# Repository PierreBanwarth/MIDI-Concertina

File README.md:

# MIDI-concertina

This is The Github project wich his a personnal work about Making an electronic version of my concertina,

Goal is to play by night with my headphones for my neighboors and maybe with my band BernyTradSchool

Arduino =>( midi library ) Serial port ( hairless midi serial ) => midi port ( loopMidi ) => Fruity Loops / Ableton / ...

We chose this solution because it's the most generic you can interface with

I use two arduinos (nano)

this project is developed with platformIO file structure.
http://platformio.org/

After the V1 done (whithout air sensor) it's look my buttons was very bad and not speed enough to play music so i have ordered some Cherry mx black keys

I have done my custom keyboard here
http://www.keyboard-layout-editor.com/#/

and use it to create the grid to plate mounted switches
http://builder.swillkb.com/

I've write tutorials here :

In english
https://www.instructables.com/id/Make-Your-MIDI-Accordion/
In french
https://ouiaremakers.com/posts/tutoriel-diy-creation-d-un-accordeon-midi

Some personnal note in french about the new version

# Le projet : petit historique
Je suis developpeur et je joue du concertina et j'aime cet instrument inventé par un physicien (https://fr.wikipedia.org/wiki/Charles_Wheatstone)

Le problème initial était de pouvoir jouer au casque la nuit et ainsi laisser ma copine dormir.

## Electronique :
Dans cet objectif la j'ai acheté mon premier Arduino à noel 2016.

Avec cet objectif en tête je me suis dabord entrainé sur un controlleur de vole spatiaux pour le jeu Kerbal Space Program.

[PHOTO DE LA BOITE EN CARTON]

ça m'a permis de comprendre le branchement des boutons et la récupération des entrée/sortie dans le code.

J'ai ensuite réalisé un premier prototype de concertina MIDI

[PHOTO DU premier PROTOTYPE]

à l'époque je n'avais pas en tête l'utilisation du protocole MIDI je sortais donc le son en 8bit sur une sortie casque.

## Le clavier et les Boutons :

Depuis le début du projet le choix a été fait de ne pas faire de matrice de boutons.

Le but est de reproduire le plus fidèlement possible le jeux sur l'instrument (dans un premier temps son clavier au moins)

Hors le multipléxage ne permet pas de jouer plusieurs notes en même temps de façon continue.

Si je tape sur 6 touches je veux obtenir six sons différents.

Hors quand on tape sur six touches de son clavier d'ordinateur simultanément : on obtiens une seul frappe.

(peut etre a mieux expliquer)

Donc chaque sortie de l'arduino sera dédié a une touche.

### Premiers boutons :

[PHOTO Des premiers boutons]

Cependant les boutons etait bas de gamme et ne reagissais parfois pas du tout a l'appuie.

Hors ce projet necessite des boutons réactifs et précs.

### CHERRY MX
Je ne me souviens pas si c'est moi ou si on m'a soufflé l'idée mais c'est vrai que les boutons de claviers mécaniques ont plusieurs avantages :

Une communauté active qui a crée :
- Des PCB personnalisés.
- Les "Footprint" des divers boutons.
- beaucoup de comparatifs des différents boutons.
- Des utilitaires en lignes comme :
http://www.keyboard-layout-editor.com/#/
http://builder.swillkb.com/
- Des lubrifiants, ressorts alternatifs et autres silencieux (en cours d'études)

L'avantage de ces switchs c'est qu'ils sont fait pour durer dans le temps, sont fiable et précis.

De plus ils ont un "top" qui permet d'adapter tout et n'importe quoi sur le dessus :

étude en cours :
- boutons de clavier :
- boutons style accordéon :
- bontons style concertina :

Merci beaucoup à toutes la communauté de Geekhack et de Reddit/CustomKeyboard pour toutes les heures de lectures.

J'ai donc fait un premier clavier (sans soufflet) qui ressemble aux claviers coupés en deux

[PHOTO DE LA VERSION 2]

Soucis rencontrés avec ce modèle : le clavier etait souder sans PCB donc par des cables.

Au niveau du temps et des manipulations ça s'est averé plutot fragile (malgré l'intervention d'un ami electronicien)

L'avantage du clavier de CONCERTINA-MIDI-V3 c'est que le PCB va finir de stabiliser les boutons

## Note sur le soufflet :
N'ayant qu'un seul concertina à cet époque la j'ai eu plusieurs idée de réalisation de soufflet custom.

Cependant devant la complexité de la chose j'ai décidé de ne pas gérer le soufflet dans un premier temps et d'utiliser un bouton à la place pour simuler le pousser/tirer.

* footswitch (pédale de guitare) : trop dur pour la main
* Bouton d'arcade : pas mal mais placé au mauvais endroit (sous la paume)
* Joystick : contre intuitif mais interessant de par les deux axes (mais on sort de l'idée de reproduction d'accordéon.)
* Cherry MX : parce que finalement c'est les meilleurs boutons qu'on puisse trouver j'ai réussi a en placer un sous mon pouce et c'etait plutôt efficace.

Cependant en 2017 j'ai acheté un nouveau concertina. Me laissant du coup l'ancien modèle libre. On en reparlera quand on evoquera l'impression 3D

## OPEN SOURCE MIDI :

Attiré depuis le début par la réalisation d'un projet a 100% Open Source et Open Hardware

Concernant le protocole MIDI j'ai entendu des choses sur des protocoles plus récent et peut être plus adapté a mon besoin.

Cependant je n'ai pas eu l'occasion ni le temps de me pencher sur ces solutions

With MIDILibrary (very easy to use for outputs)
http://playground.arduino.cc/Main/MIDILibrary

Good for interface with a virtual midi port and to test while developing
http://projectgus.github.io/hairless-midiserial/

to test and interface with Hairless Midi <-> Serial
http://www.tobias-erichsen.de/software/loopmidi.html

## RASPBERRY AS MIDI SYNTH.

Après la version 2.0 j'ai appris quelques morceaux les nuits d'insomnie, je me suis bien amusé a jouer de la guitare electrique et des sons MIDI vraiments moches

Cependant un nouveau besoin est arrivé, j'avais 2x45 minutes de trajets en bus par jour donc pourquoi pas profiter de ce temps "mort" pour jouer du concertina MIDI

J'ai donc cherché une solution et découvert que le Raspberry pouvait remplir la fonction de synthé MIDI.

Alors on ajoute une batterie pour alimenter le raspberry, On lance le démarrage du synthé MIDI, et on connect ça aux arduinos.

[Peut être mettre ici un tuto sur l'installation du synthé et son démarrage automatique]

plus qu'a choisir le son et on peux jouer en branchant un prise jack a la solution existante.

Cette version répond au besoin mais pause de nouvelles intérogations et ouvre un nouveau chant des possible

Nouveaux défi :
- laisser un raspberry dans la solution et permettre de brancher quand meme les deux mains de l'accordéon a un ordinateur
- intégrer la batterie a la solution => recharchement / boutons on/off

## NUMEROTATION DES VERSIONS ET MODELE ECONOMIQUE

Au fil de l'eau j'ai décidé d'un systême de notation des versions

les versions supérieurs verront un nouveau systême soit sur le clavier soit le soufflet voir les deux

et on passera a 3.5 sur une version portable (avec raspberry intégré)

J'ai réalisé qu'une seul main sans gestion du soufflet correspondais un petit clavier MIDI sans Matrice qui peux servir pour la musique electronique

Vu que le projet est Open Source vous n'aurez pas besoin de moi pour refaire tout de A à Z mais vous risquez d'y passer du temps.

J'ai donc opté pour une solution de vente du style Tyndie ou je vendrais
- le circuit imprimé
- le circuit imprimé + Arduino + Cherry MX + Boitier + vis etc..

https://www.tindie.com/

peut etre aussi une solution du style Pay me a coffee.

## GESTION DU SOUFFLE
  On a vu à travers l'impression 3D qu'on pouvais enfin sans abimer l'ancien concertina recreer des boitiers

  On peux donc placer un capteur de préssion.

  Mais on doit faire attention a la circulation de l'air :

    - attention a laisser passer de l'air (comme si on appuyais en permanence sur un bouton)

    - laisser passer de l'air implique une soupape (Gros trou ouvrable a l'aide d'un bouton pour reprendre ou relacher beaucoup d'air d'un coup)

# CONCERTINA MIDI V3.1
Le nouvelle version comporte deux avancés majeurs :
* gestion de l'air réaliste
* circuit imprimé pour les boutons et le BME280

## Impression 3D :
C'est en arrivant vivre à Rennes que j'ai découvert l'imprimante 3D d'un ami.
[PHOTO DU TRUMP 3D]

J'en ai acheté une peux de temps après, j'ai cependant fait l'erreure d'acheter une Geeetech I3 PRO B que je n'ai jamais vraiment réussi a maitriser.
[PHOTO DE MON IMPRIMANTE]

J'ai donc fini par prendre contact avec un imprimeur sur Rennes (https://www.hephaprint.fr/)

Au début l'idée c'était de faire une grille spécial pour mon nouveau concertina et c'etait l'occasion de faire connaissance :
[PHOTO DU CONCERTINA BLEU]

C'est un peu plus tard que je me suis rendu compte que si on pouvais imprimer le haut du boitier on pouvais du coup faire le bas

Et ainsi mettre le clavier déja réalisé dans une boite étanche et a la taille exact du soufflet.

Ce qui finalement nous permettrait de mettre un capteur de préssion pour gagner en réalisme.

Nous avons donc pris les côtes de mon premier concertina et réalisé un boitié en PET.
[PHOTO DE LA BOITE NOIRE]

## MY OWN PCB
Petit feedback sur la réalisation d'un circuit imprimé pour les boutonsn, le capteur de préssion et l'arduino

Tester c'est douter ?

J'ai réalisé deux plaques a l'heure ou j'ecrit ça et j'espere que la troisieme version sera la derniere.

Soucis de la première : Les boutons sont trop écartés et la plaque est trop grande

Soucis de la deuxième et de la premiere aussi du coup : Problème de branchement sur le capteur de préssion BME 280

Avant de réaliser un circuit bien penser a tester, je me suis fait un petit excès de confiance et ça m'a couté 40 balles

Pour réaliser le circuit je me suis inspiré de ça :
https://github.com/ruiqimao/keyboard-pcb-guide

Après sur l'utilisation de KiCad et LibreCad c'est long, dur, ingras.

Un peu compliqué de créer un circuit quand tu as rapidement bidouillé des Arduinos et que tu passes en mode ingenierie serieuse et définitive (20$ par essai).

la grande difficulté de ce projet c'est la maitrise des outils logiciels.

## Placer le circuit sur la grille du concertina.

Une fois le PCB crée il faut réaliser la grille en métal dans laquelle iront se loger les boutons
pour ça j'ai extrait dans un dxf le haut du boitié réalisé avec l'imprimeur 3D
une fois supprimé les détails inutils pour la grille j'ai intégré une extraction de la couche F.Skills de mon projet KiCad

## Raspberry PI
J'ai récemment réfléchie a une nouvelle solution ou le raspberry Pi centraliserais les entrées des différents arduino
via un programme python je récupere les entrées MIDI des deux Arduino
Un switch ON/Off
- ON : on envoie du son via la prise jack raspberry
- OFF : on envoie du MIDI via une prise USB

## Test
Pour tester le capteur de préssion on va essayer de voir les différentes variations de préssions a l'interieur de l'instrument
Pour cette experience j'ai mis une des anciennes mains présentes sur mon instrument d'origine et j'ai mis un boitié imprimé en 3D.
J'ai tenté de boucher les entrées / sorties d'air de la version imprimé en 3D et j'ai placé le capteur de préssion

TODO poster ici les courbes de pression

## Prix de la V3
Parlons du prix de tout ça maintenant:
### Frais déja engagés

* 3 Arduino PRO (un est deja décédé (inversion gnd et 5v sur le BME280) : EUR 15,99
* 2 capteurs de Pression BME280EUR 6,76
* 40 switchs cherry Mx : 40$
* 2 Boitiers (design + impression) : 70$
* 2 repose poignet (design + impression) : 10$
* 2 Grilles test pour validation dxf grille : 25$
* 10 PCB Grille v2.9 : 25$
* 10 PCB Grille v3.0 : 25$

### frais à Engager :
* 10 PCB Grille V3.1 : 25$
* 2 Grilles découpe laser : 50$
* 2 sangles en cuir : 30$

Soit pour l'instant 306 euros on peux distinguer le cout R&D et le cout réel de l'objet
Le prix d'un soufflet et de la mécanique soupape est exclu :

### Cout d'un concertina MIDI
* Composant electroniques
     * 2 Arduino Pro : 10$
     * 2 capteurs de Pression BME280 : 10$
     * 10 PCB Grille V3.1 : 25$
     * 30 switchs cherry Mx : 30$
     * 2 Grilles découpe laser : 50$
* Cordonnerie :
     * 2 sangles en cuir : 30$
* Impression 3D :
     * 2 Boitiers (design + impression) : 70$
     * 2 repose poignet (design + impression) : 10$
* Total : 235$

## Reflexion sur la V3.5
Le but serait ici de rajouter un raspberry, une batterie et son systeme de rechargement + gestion ON/OFF
On pourrait ainsi jouer au casque directement sur l'instrument. De plus brancher deux cables en facades en direction d'un ordinateur nous permettra d'utiliser l'instrument avec Ableton etc..

- [ ] Rechargement de la batterie
- [ ] Capacité de la batterie minimal de 5h
- [ ] Possibilité de faire On/Off sur l'alimentation
- [ ] Couper la liaison Arduino -> Raspberry quand on plug un Arduino -> PC
- [ ] que toute les prises soit sur la même face de l'hexagone.

sorties prévues en facade :
- sortie casque (output son raspberry)
- prise usb 1 (pour arduino 1)
- prise usb 2 (pour arduino 2)
- prise usb 3 pour recharge batterie du raspberry
- switch on/off pour alimentation raspberry

=?= capteur de pression=?=

- comment partager l'info du bmp 280 ?
- combien d'entrée ça prend un bmp 280 ? Réponse : 4
-> Update i2C => deux entrées
- pour avoir une valeur normative on pourrait faire un differenciel avec un autre bmp 280 placé dans le clavier
- dans les deux cas comment on fait passer la même info des deux côtés de l'instrument ?

=?= question physiques=?=

- cableries avec étanchéité ?
- Un trou de taille variable pourrait permettre de tester les influences différentes d'un trou qui simule un bouton ouvert.
- Gestion de l'air on passe de pousser/tirer a pousser/rien/tirer

=?= clavier=?=

- Boutons custom ?
https://www.massdrop.com/buy/gateron-switches
- Cercle silicon ?
- lubrification des boutons ?
- achat de clip qui se posent sur le switch avec 30% de réduction du bruit ?

=?= Couleurs=?=
- LED ? on pourrait ajouter un arduino pour gerer les leds eventuels ?

RASPBERRY integration
- Deux boards FTDI
- par défaut branché au raspberry
- si branché a un pc raspberry annulé

- Une batterie
- branché au raspberry
- bouton on/off pour l'alimentation
- sortie de recharge en exterieur
- Sortie casque

intérèt d'imprimer une version test sans soupape du boitier imprimé en 3D
- tester et valider la forme des boites
- tester et valider les entrées et les boutons
- valider installation capteur de préssion
- tester pour savoir ce qu'on peux ajouter et comment

Dans un premier temps on fera pas de FTDI on en a besoin pour la version 3.5 qui sera elle tout embarqué

la différence avec mon projet :

- pas dematrice
- plus simple d'utiliser la footprint de l'arduin plutot que de mettre un Atmega sur la board (surtout niveau soudure)

Point d'avancement 01/02/2019 :

Le prototype de boite 3D semble parfait pour l'usage qu'on en fait j'irais chercher la deuxieme boite bientôt.
Le PCB changeant régulierement le travail sur le dessin de la grille se retrouve toujours décallé a plus tard.

<<<<<<< HEAD

BUILD LOG

Faire un journal de bord c'est se rendre compte qu'on aurais du écouter les gens qui nous ont conseillés
cependant il semble que la pin13 de l'arduino soit reconnu a l'etat LOW a cause d'une resistance et d'une LED qui y sont branchés
https://forum.arduino.cc/index.php?topic=328387.0
Visiblement il se peux que rajouter une resistance dans le circuit puisse changer la donne.
=======
Alors 13, 16 et 17 c'est des entrées de merdes qui marchent pas comme des grosses connasses
>>>>>>> a101e9a32d0ce61c1e40775b79481c0ef097a120

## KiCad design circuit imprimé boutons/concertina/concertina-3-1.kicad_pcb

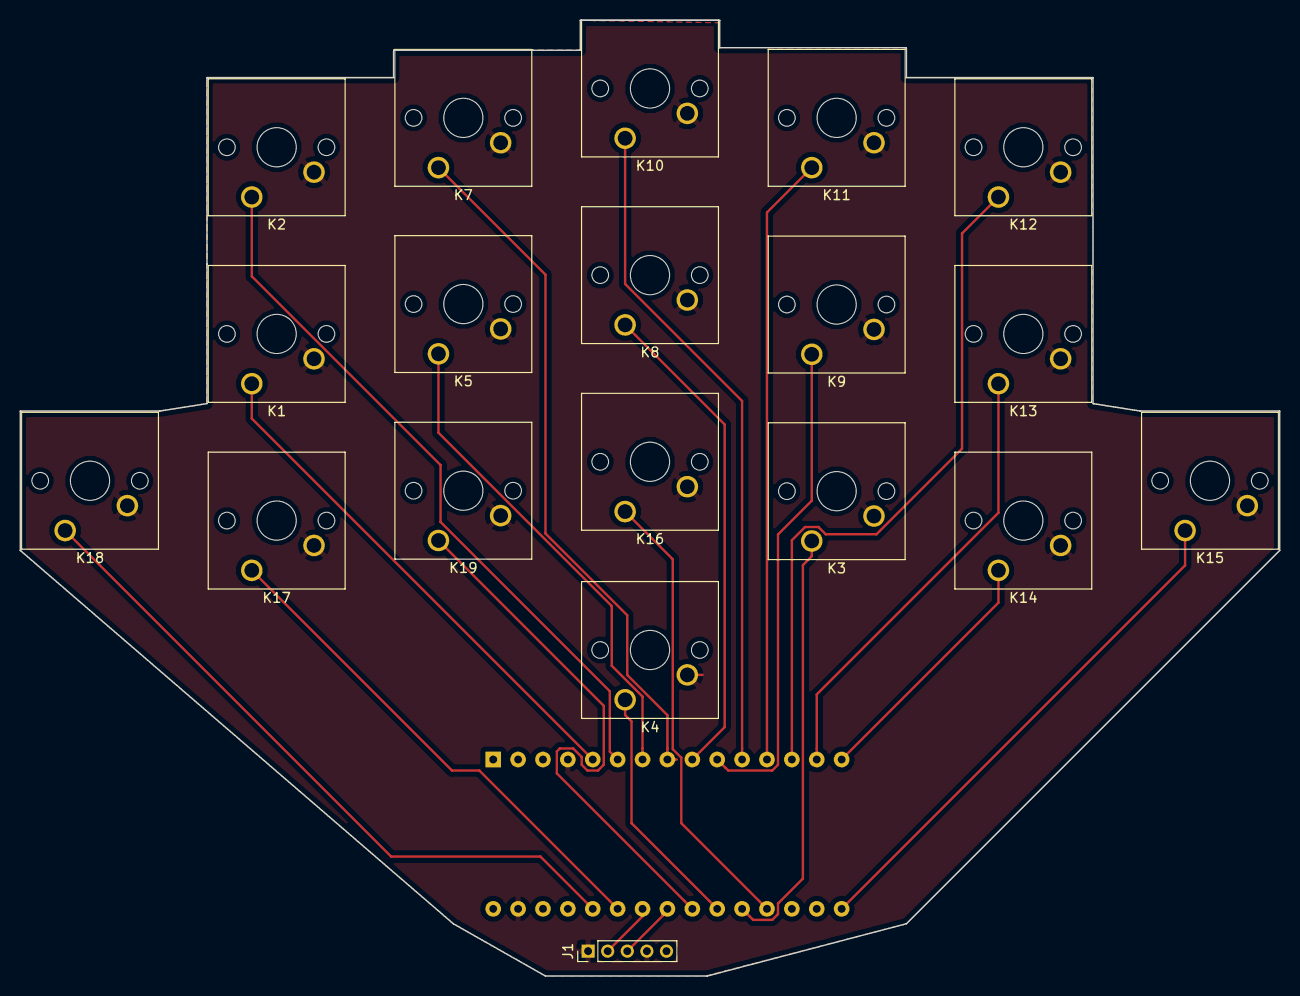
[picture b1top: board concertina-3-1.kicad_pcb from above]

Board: 2 copper layers, 128.5 x 97.5 mm, 20 parts (1 on the bottom side), 22 nets.

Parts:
A1: Arduino_Nano_v3.x; Arduino_Nano
J1: Conn_01x05_Male; PinHeader_1x05_P2.00mm_Vertical
K1, K2, K3, K4, K5, K7, K8, K9, K10, K11, K12, K13, K14, K15, K16, K17, K18, K19: KEYSW; SW_Cherry_MX1A_1.00u_PCB

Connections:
GND: A1.4, A1.29, J1.1, J1.4, K1.2, K2.2, K3.2, K4.2, K5.2, K7.2, K8.2, K9.2, K10.2, K11.2, K12.2, K13.2, K14.2, K15.2, K16.2, K17.2, K18.2, K19.2
unnamed: A1.5, K1.1
unnamed: A1.6, K2.1
unnamed: A1.7, K5.1
unnamed: A1.8, K7.1
unnamed: A1.9, K8.1
unnamed: A1.10, K9.1
unnamed: A1.11, K10.1
unnamed: A1.12, K11.1
unnamed: A1.13, K12.1
unnamed: A1.14, K13.1
unnamed: A1.15, K14.1
unnamed: A1.16, K15.1
unnamed: A1.17, J1.5
unnamed: A1.19, K16.1
unnamed: A1.20, K3.1
unnamed: A1.21, K4.1
unnamed: A1.22, K19.1
unnamed: A1.23, J1.3
unnamed: A1.24, J1.2
unnamed: A1.25, K17.1
unnamed: A1.26, K18.1

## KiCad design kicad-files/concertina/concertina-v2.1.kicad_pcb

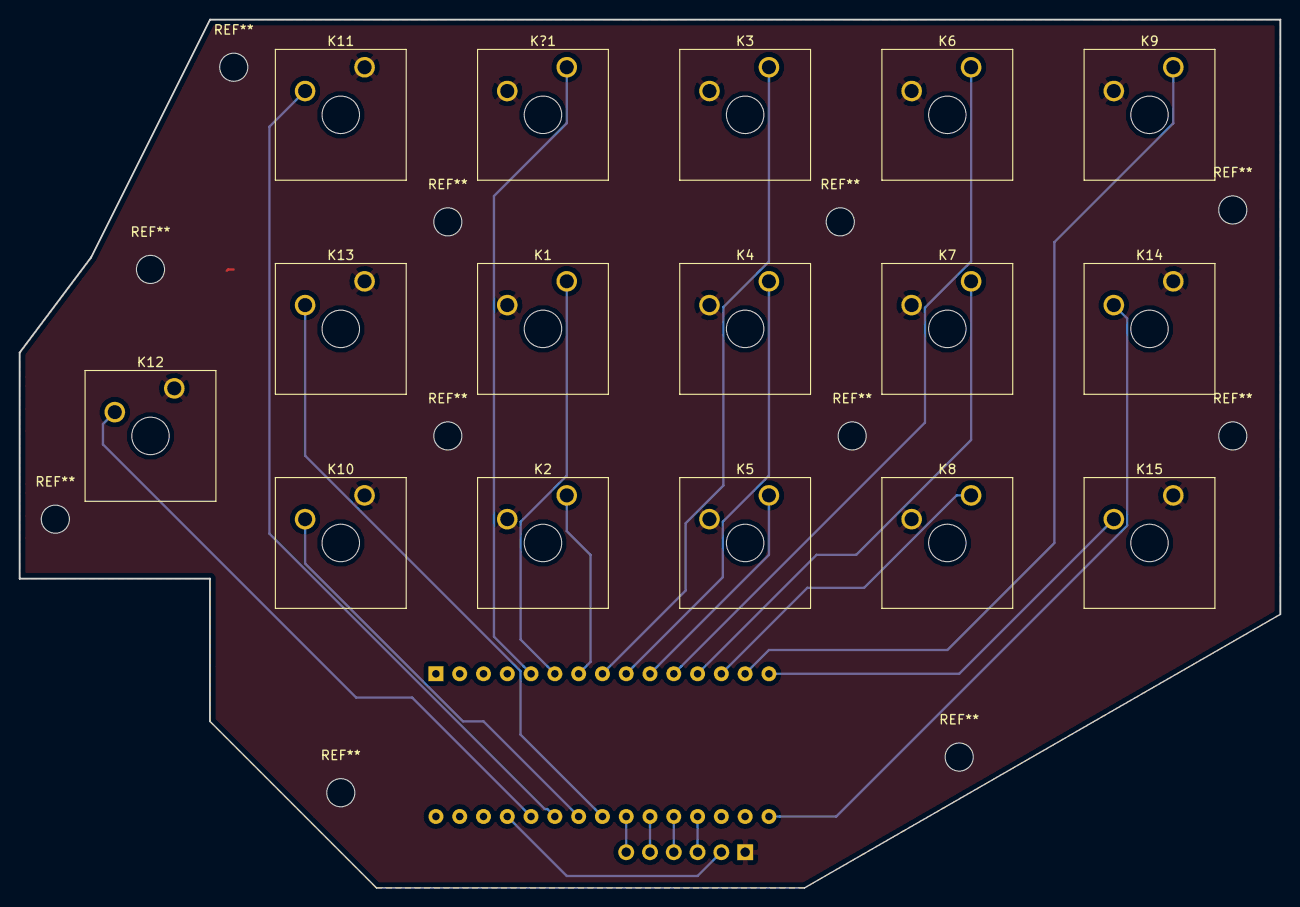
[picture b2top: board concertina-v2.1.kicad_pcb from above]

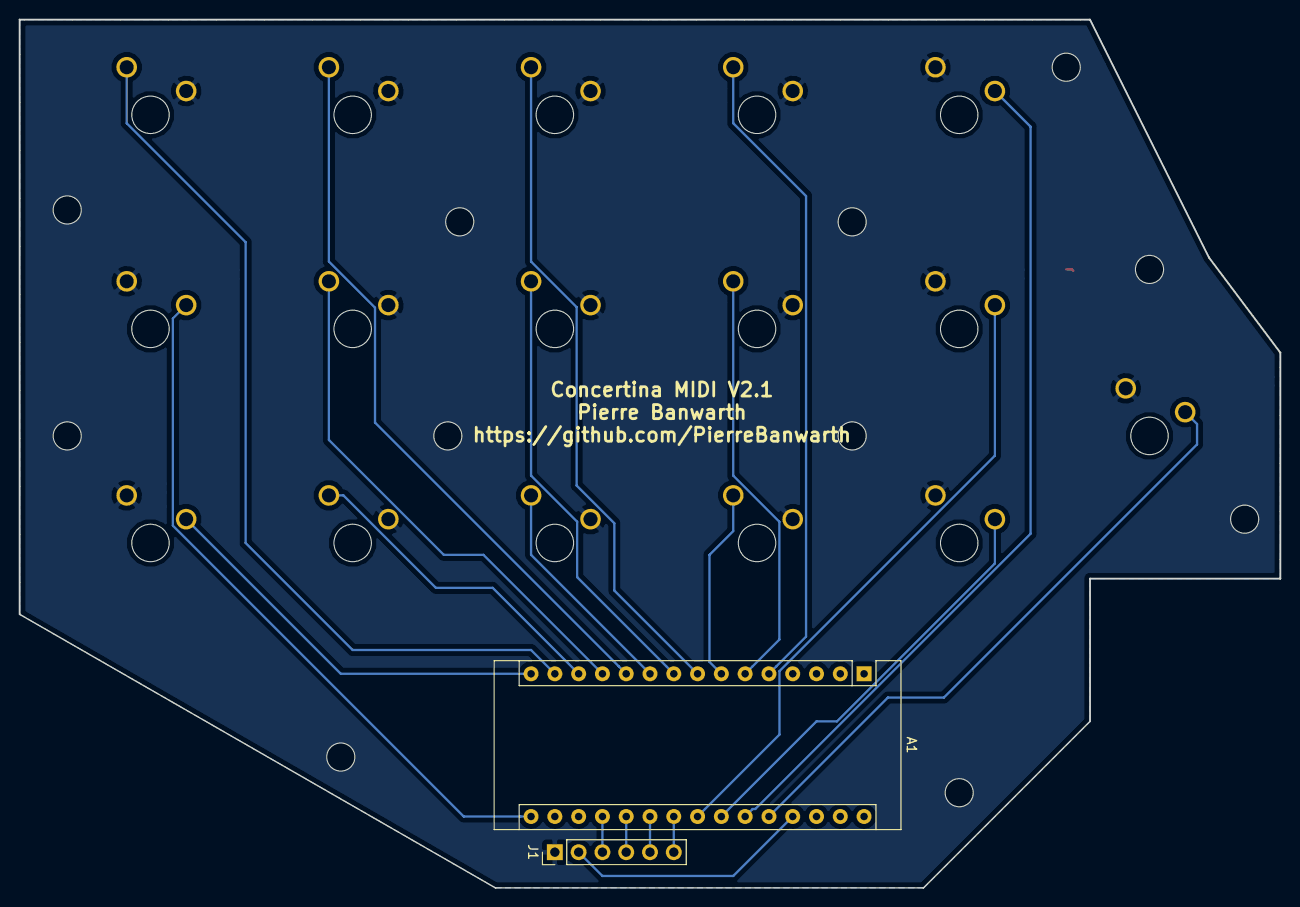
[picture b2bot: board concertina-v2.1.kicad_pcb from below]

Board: 2 copper layers, 134.6 x 92.7 mm, 18 parts (2 on the bottom side), 22 nets.

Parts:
A1: Arduino_Nano_v3.x; Arduino_Nano
J1: Conn_01x06_Male; PinHeader_1x06_P2.54mm_Vertical
K1, K2, K3, K4, K5, K6, K7, K8, K9, K10, K11, K12, K13, K14, K15: KEYSW; SW_Cherry_MX1A_1.00u_Plate
K?1: KEYSW; SW_Cherry_MX1A_1.00u_Plate

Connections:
GND: J1.1, K1.2, K2.2, K3.2, K4.2, K5.2, K6.2, K7.2, K8.2, K9.2, K10.1, K11.1, K12.1, K13.1, K14.1, K15.1, K?1.2
unnamed: A1.5, K?1.1
unnamed: A1.6, K1.1
unnamed: A1.7, K2.1
unnamed: A1.8, K3.1
unnamed: A1.9, K4.1
unnamed: A1.10, K5.1
unnamed: A1.11, K6.1
unnamed: A1.12, K7.1
unnamed: A1.13, K8.1
unnamed: A1.14, K9.1
unnamed: A1.15, K15.2
unnamed: A1.16, K14.2
unnamed: A1.19, J1.3
unnamed: A1.20, J1.4
unnamed: A1.21, J1.5
unnamed: A1.22, J1.6
unnamed: A1.23, K13.2
unnamed: A1.24, K10.2
unnamed: A1.25, K11.2
unnamed: A1.26, K12.2
unnamed: A1.27, J1.2

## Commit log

2016-05-30 :confetti_ball: Added .gitattributes & .gitignore files
2016-05-30 First commit
    First scanning key algorythm need to be optimized,
2016-05-30 adding file for platformIO changing type of all int, ready for the unique code version for both arduino.
2016-05-30 Adding comments on arduino code
    Adding comments
2016-05-31 platform.io configuration updated for both arduino nano and uno, look more speed
2016-06-08 update progress to V2
2016-06-08 Adding keyboard griid plans
2016-08-18 untested addition of minimum play time for each tune
2017-05-23 Update from old dev
2017-06-02 Update README.md
    adding tutorials links
2018-10-23 adding file to descripe pcb and mounting plate for next version
2018-10-23 Update README.md
    update about project
2018-10-26 personnel reflexions added to readme.md to stop thinking about this all time
2018-10-26 Update README.md
    some research
2018-10-30 First version of PCB done !
2018-11-04 Adding BMP 280 connectors, adding one key for some tests and lot of mounting holes
2018-11-06 Adding FTDI informations
    I plan to add ftdi to the board
2018-11-13 new cool stuff
2018-11-13 Adding reflections about first box print value
2019-03-12 adding a lot of files for PCB and 3D printed parts
2019-03-12 Create successfull-test
2019-03-12 removing old files
2019-03-19 test
2019-04-04 adding test
2019-04-08 working keyboard, working through time pressure measurements
2020-04-26 pressure
2020-05-01 some optimizations
2022-02-27 tesr
